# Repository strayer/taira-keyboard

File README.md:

# Taira Keyboard

## What?

A wireless low-profile split mechanical keyboard with 66 keys inspired by the
ErgoDash and Corne Chocolate. It runs ZMK on two nice!nanos, is fully wireless
via Bluetooth and uses Kailh Choc V1 switches in a 18x19mm grid layout.

## Why?

I used an ErgoDash with MX switches for over a year multiple hours each day.
Even though I love typing on it, it always felt too bulky and the wires really
started to annoy me - especially when moving between workplaces. At some point I
discovered ZMK and started plans on building a keyboard based on the ErgoDash,
but as low-profile as I could manage.

After investigating which other low-profile keyboards exist in the community, I
quickly realized that the most sophisticated offer seems to be the Corne
Chocolate. This keyboard is heavily based upon the footprints of the Corne
Chocolate, but layed out in a layout very similar to the original ErgoDash.

### ErgoDash comparison

## Build guide

Follow the [build guide](BUILDGUIDE.md) if you are interested in building your
own Taira.

## Firmware

The ZMK firmware is managed in a separate repository: [strayer/taira-keyboard-zmk-config]

[strayer/taira-keyboard-zmk-config]: https://github.com/strayer/taira-keyboard-zmk-config

## Acknowledgements

Thanks to [@omkbd](https://github.com/omkbd) and
[@foostan](https://github.com/foostan/) for releasing both the ErgoDash and the
Corne Chocolate under the MIT license. Without their work, this keyboard would
not exist.

- https://github.com/omkbd/ErgoDash
- https://github.com/foostan/crkbd/tree/main/corne-chocolate
- an unnamed coworker who helped me _a lot_ while planning and working on the
  keyboard

## Copyright

Copyright 2022 Sven Grunewaldt

License: [MIT](LICENSE)

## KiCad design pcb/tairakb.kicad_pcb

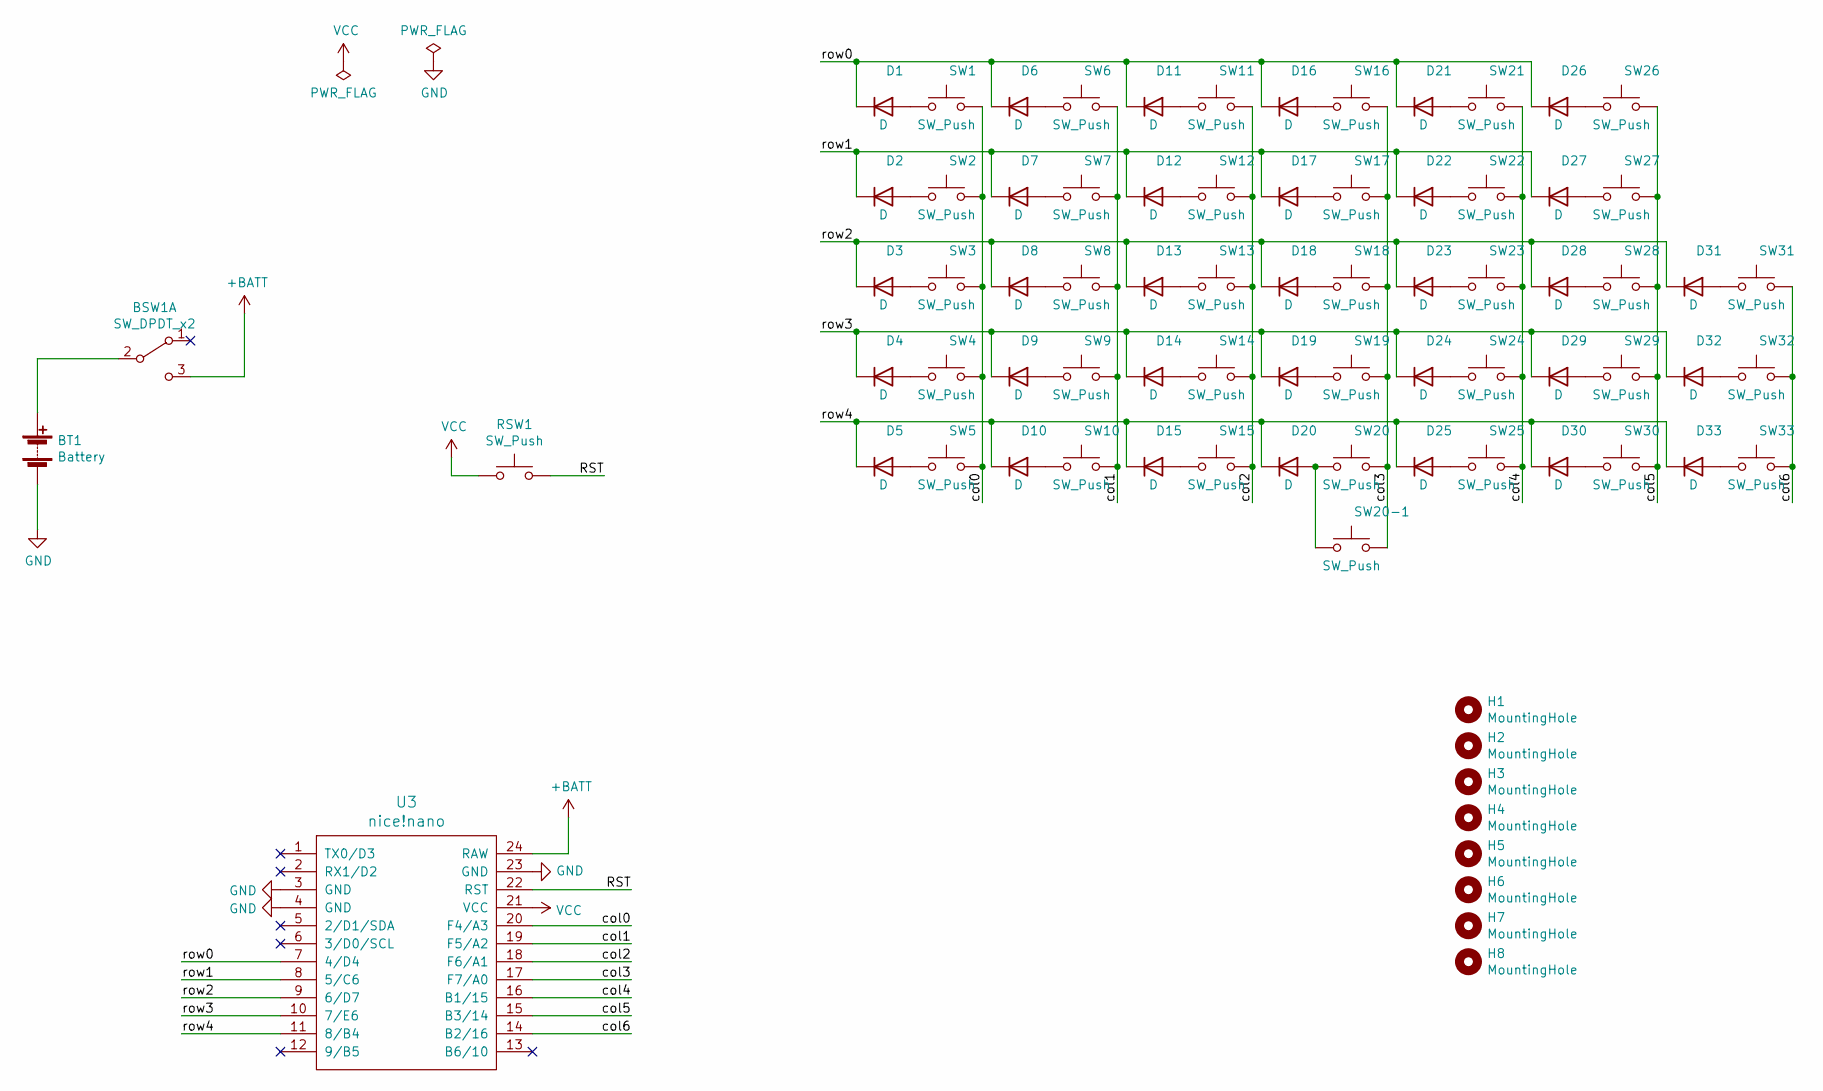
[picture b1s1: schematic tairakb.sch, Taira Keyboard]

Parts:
BSW1: SW_DPDT_x2; SS-12D00
BT1: Battery; Battery_Wire_Connector
D1, D2, D3, D4, D5, D6, D7, D8, D9, D10, D11, D12, D13, D14, D15, D16, D17, D18, D19, D20, D21, D22, D23, D24, D25, D26, D27, D28, D29, D30, D31, D32, D33: D; D3_SMD
H1, H2, H3, H4, H5, H6, H7, H8: MountingHole; LEGO_HOLE
RSW1: SW_Push; ResetSW
SW1, SW2, SW3, SW4, SW5, SW6, SW7, SW8, SW9, SW10, SW11, SW12, SW13, SW14, SW15, SW16, SW17, SW18, SW19, SW20, SW20-1, SW21, SW22, SW23, SW24, SW25, SW26, SW27, SW28, SW29, SW30, SW31, SW32, SW33: SW_Push; Choc_Hotswap
U3: nice!nano; nicenano

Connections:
+BATT: BSW1.3 (C), U3.24 (RAW)
/RST: RSW1.2, U3.22 (RST)
/col0: SW1.2, SW2.2, SW3.2, SW4.2, SW5.2, U3.20 (F4/A3)
/col1: SW6.2, SW7.2, SW8.2, SW9.2, SW10.2, U3.19 (F5/A2)
/col2: SW11.2, SW12.2, SW13.2, SW14.2, SW15.2, U3.18 (F6/A1)
/col3: SW16.2, SW17.2, SW18.2, SW19.2, SW20.2, SW20-1.2, U3.17 (F7/A0)
/col4: SW21.2, SW22.2, SW23.2, SW24.2, SW25.2, U3.16 (B1/15)
/col5: SW26.2, SW27.2, SW28.2, SW29.2, SW30.2, U3.15 (B3/14)
/col6: SW31.2, SW32.2, SW33.2, U3.14 (B2/16)
/row0: D1.1 (K), D6.1 (K), D11.1 (K), D16.1 (K), D21.1 (K), D26.1 (K), U3.7 (4/D4)
/row1: D2.1 (K), D7.1 (K), D12.1 (K), D17.1 (K), D22.1 (K), D27.1 (K), U3.8 (5/C6)
/row2: D3.1 (K), D8.1 (K), D13.1 (K), D18.1 (K), D23.1 (K), D28.1 (K), D31.1 (K), U3.9 (6/D7)
/row3: D4.1 (K), D9.1 (K), D14.1 (K), D19.1 (K), D24.1 (K), D29.1 (K), D32.1 (K), U3.10 (7/E6)
/row4: D5.1 (K), D10.1 (K), D15.1 (K), D20.1 (K), D25.1 (K), D30.1 (K), D33.1 (K), U3.11 (8/B4)
GND: BT1.2 (-), U3.3 (GND), U3.4 (GND), U3.23 (GND)
unnamed: BSW1.2 (B), BT1.1 (+)
unnamed: D1.2 (A), SW1.1
unnamed: D2.2 (A), SW2.1
unnamed: D3.2 (A), SW3.1
unnamed: D4.2 (A), SW4.1
unnamed: D5.2 (A), SW5.1
unnamed: D6.2 (A), SW6.1
unnamed: D7.2 (A), SW7.1
unnamed: D8.2 (A), SW8.1
unnamed: D9.2 (A), SW9.1
unnamed: D10.2 (A), SW10.1
unnamed: D11.2 (A), SW11.1
unnamed: D12.2 (A), SW12.1
unnamed: D13.2 (A), SW13.1
unnamed: D14.2 (A), SW14.1
unnamed: D15.2 (A), SW15.1
unnamed: D16.2 (A), SW16.1
unnamed: D17.2 (A), SW17.1
unnamed: D18.2 (A), SW18.1
unnamed: D19.2 (A), SW19.1
unnamed: D20.2 (A), SW20.1, SW20-1.1
unnamed: D21.2 (A), SW21.1
unnamed: D22.2 (A), SW22.1
unnamed: D23.2 (A), SW23.1
unnamed: D24.2 (A), SW24.1
unnamed: D25.2 (A), SW25.1
unnamed: D26.2 (A), SW26.1
unnamed: D27.2 (A), SW27.1
unnamed: D28.2 (A), SW28.1
unnamed: D29.2 (A), SW29.1
unnamed: D30.2 (A), SW30.1
unnamed: D31.2 (A), SW31.1
unnamed: D32.2 (A), SW32.1
unnamed: D33.2 (A), SW33.1
VCC: RSW1.1, U3.21 (VCC)

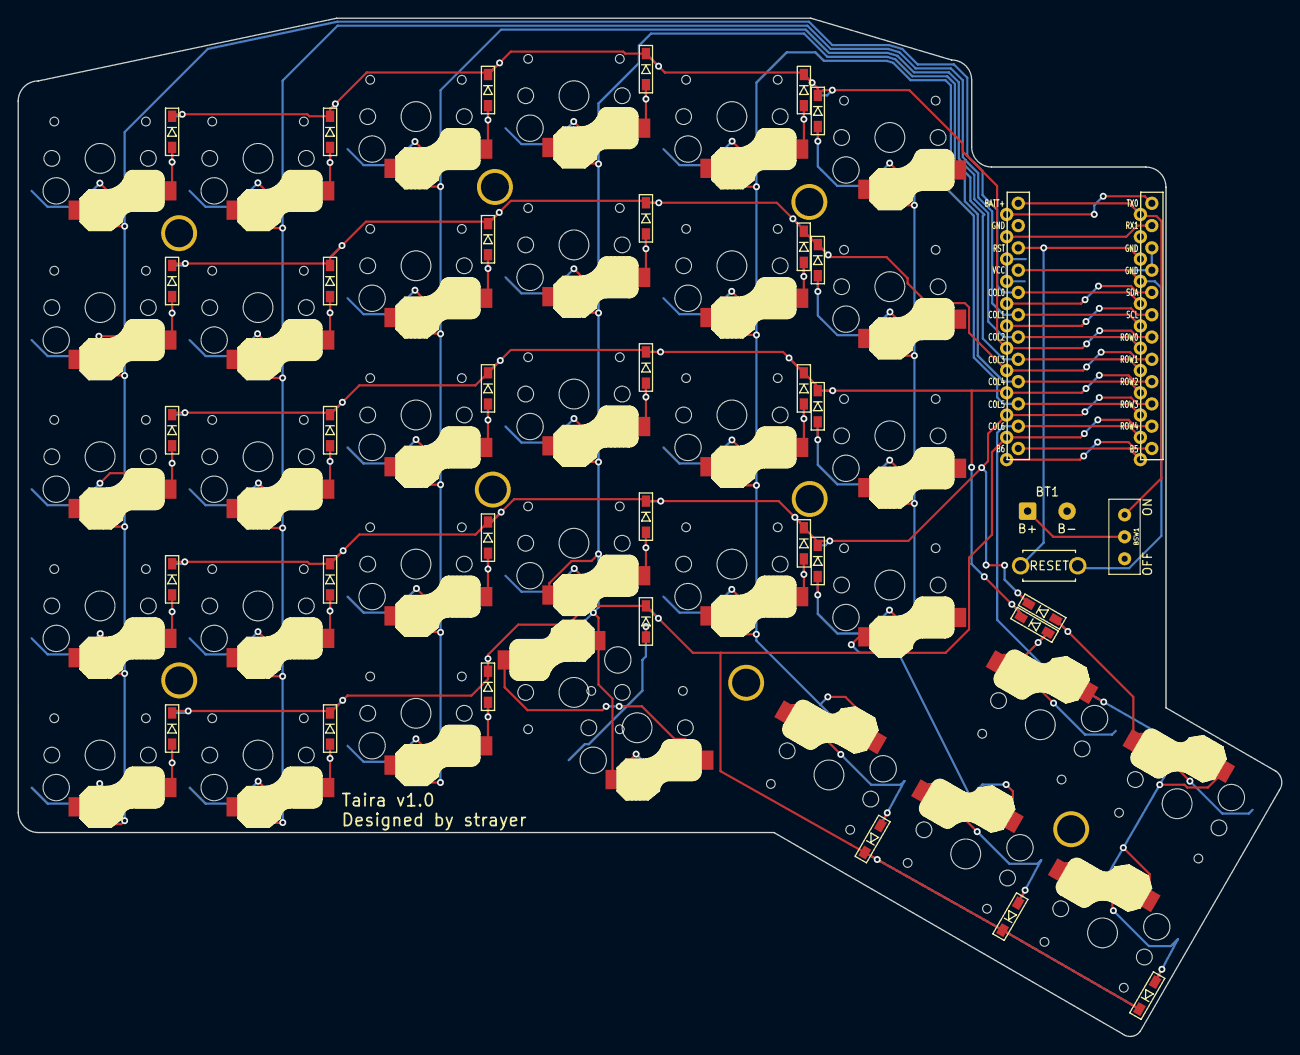
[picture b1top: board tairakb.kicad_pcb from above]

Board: 2 copper layers, 144.0 x 116.0 mm, 79 parts (0 on the bottom side), 50 nets.

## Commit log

2021-12-07 Add first draft of Taira Keyboard
2021-12-07 Remove unnecessary PWR_FLAG
2021-12-07 Fix incorrect switch cutout on top plate
2021-12-07 Add traces routed by hand
    Previously the diodes were connected from the columns to the switches.
    Both the ErgoDash and the Corne have them behind the switches connected
    to the rows. Since I positioned the diodes on the PCB like they are in
    the ErgoDash and Corne, the routing was much more difficult than intended.
    This moves the diodes behind the switches and also moves them around a
    bit on the PCB. This allowed me to hand route all traces easily, so this
2021-12-07 Add revision 1.0
    Pretty much everything changed. A lot of things were fixed, plates were
    added and the spacing between the keys is now 1mm (there was no spacing
    before).
2022-02-03 Add documentation
2022-02-09 Add ErgoDash comparison image to README
2022-04-01 Bump minimist from 1.2.5 to 1.2.6
    Bumps [minimist](https://github.com/substack/minimist) from 1.2.5 to 1.2.6.
    - [Release notes](https://github.com/substack/minimist/releases)
    - [Commits](https://github.com/substack/minimist/compare/1.2.5...1.2.6)
    ---
    updated-dependencies:
    - dependency-name: minimist
2022-04-08 Upgrade nodejs dependencies
    Note: These are only used when editing the documentation files.
2022-07-28 Update BUILDGUIDE.md
    Part numbers for switches were swapped.
2025-11-15 Bump js-yaml from 4.1.0 to 4.1.1
    Bumps [js-yaml](https://github.com/nodeca/js-yaml) from 4.1.0 to 4.1.1.
    - [Changelog](https://github.com/nodeca/js-yaml/blob/master/CHANGELOG.md)
    - [Commits](https://github.com/nodeca/js-yaml/compare/4.1.0...4.1.1)
    ---
    updated-dependencies:
    - dependency-name: js-yaml

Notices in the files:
pcb/tairakb.kicad_pcb:
Licensed under the MIT License - Copyright (c) 2021 Sven Grunewaldt
parts and their libraries:
Mini power slide switch – Licensed under CC-BY-SA-4.0 (based on https://github.com/kaibader/KiCad-Library)
Licensed under MIT, Based on https://github.com/foostan/kbd/blob/master/kicad-footprints/kbd.pretty/ProMicro_v2.kicad_mod
